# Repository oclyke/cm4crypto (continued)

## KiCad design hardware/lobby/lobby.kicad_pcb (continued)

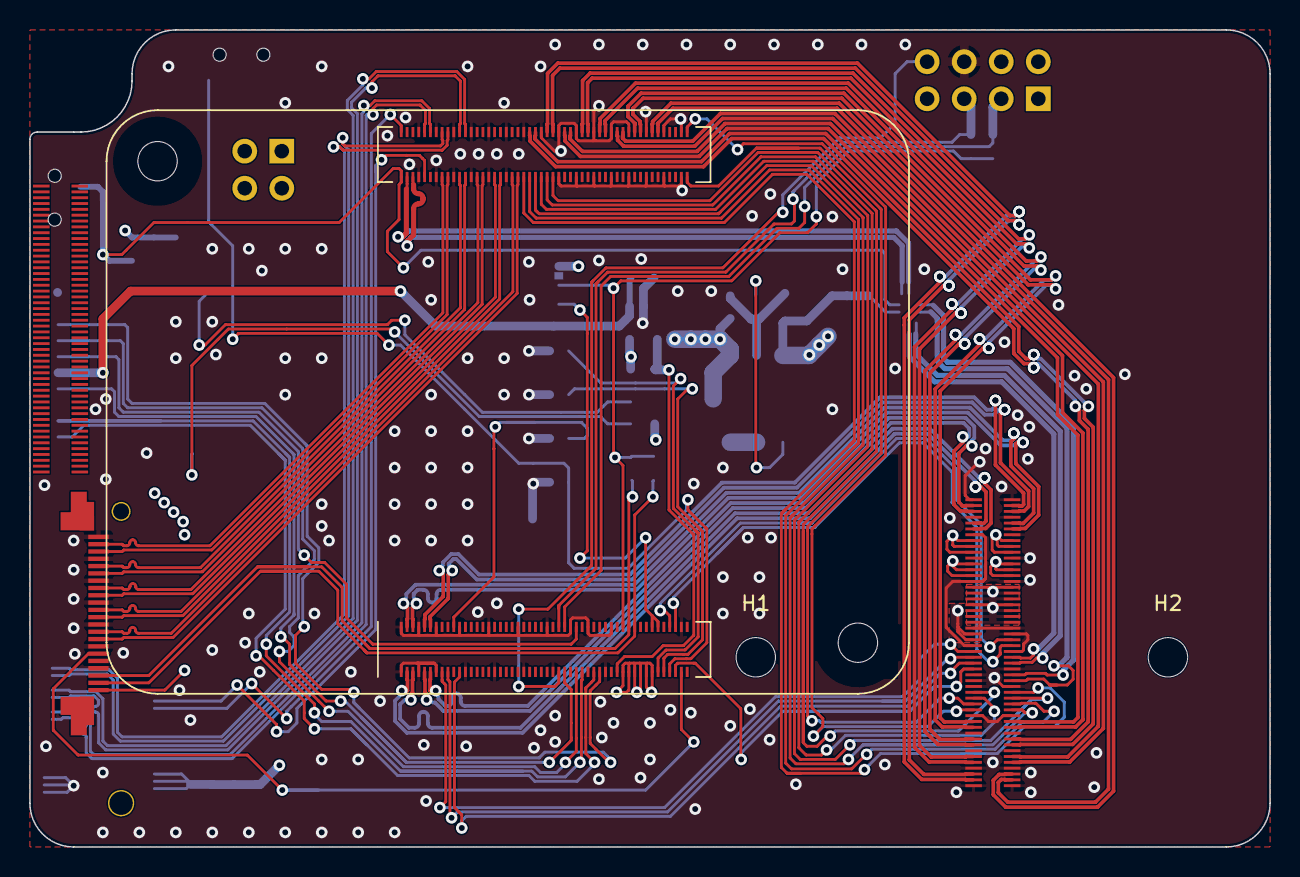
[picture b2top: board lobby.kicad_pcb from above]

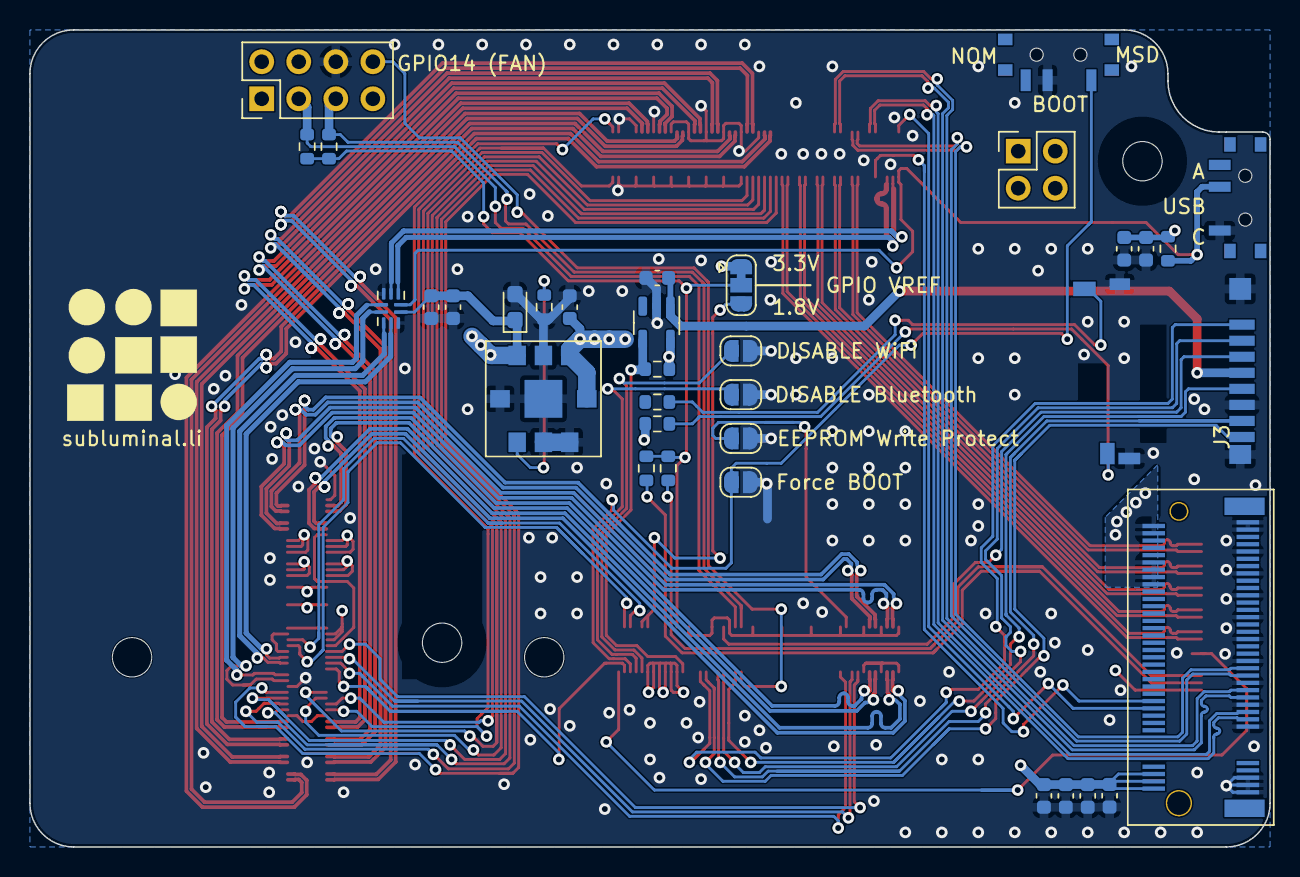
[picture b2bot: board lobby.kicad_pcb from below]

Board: 4 copper layers, 85.0 x 56.0 mm, 40 parts (34 on the bottom side), 93 nets.

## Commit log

2021-05-04 initial commit
    this contains one schematic with pretty much all the necessary bits
    todo: break into two parts for upper and lower pcbs
2021-05-04 initial commit
    planned out project structure and completed schematic for 'lobby' board
    schematic for 'mezzanine' board todo
2021-05-06 start routing mezzanine
    making a progress capture before trying to cram a lot of signals onto just one hirose connector...
2021-05-06 finished mezzanine signal routing
2021-05-13 remove backups
2021-05-13 sheet refs relative, copied escalator pinout to lobby
2021-05-31 move structural hirose connector
    to match location on the lobby board
2021-05-31 work abroad
    did some light planning for the lobby board while on vacation. now ready for final placement + routing
2021-05-31 Update fp-info-cache
    not sure what this is...
2021-05-31 addtl hdmi routing
2021-05-31 Update fp-info-cache
2021-05-31 place lobby components
2021-06-02 attempt to route gpio
2021-06-02 removed gpio from lobby to simplify routing
2021-06-03 finish routing on lobby
2021-06-03 run drc on mezzanine
2021-06-03 update hdmi and usbc footprints for router cut
2021-06-03 adjust USB dp tune
2021-06-03 tweak lobby
    pushed traces for wifi clearance zone
    improved cm4 footprint
    improved usb-c footprint
2021-06-04 tweak mezzanine
    almost ready to order
2021-06-04 update lobby
2021-06-04 update mezzanine
2021-06-04 run cam
2021-06-04 add cam zips
2021-06-07 clean up
2021-06-15 mirror lobby mezzanine connector
    fixing a big whoops
2021-06-15 modify footprints
    add paste on hdmi and usbc
    add silkscreen outline on murata dcdc supply
    change PS cap footprint to polarized footprint
2021-06-15 update silkscreen
2021-06-15 cam v2
2021-07-06 change lobby hirose connectors to the DS variant
2021-07-06 move m.2 adaptor mount hole
2021-07-06 relabel switches
2021-07-07 update camera connector footprint
2021-07-07 update USB-A host capacitor footprint
2021-07-07 regenerate gerbers
2021-07-07 satiate kicad
2021-07-10 update m.2 connector footprint
2021-07-10 change fusb42mx to qfn package
2021-07-10 regenerate cam
2021-07-10 add logo
2021-07-10 regen cam data
2021-07-10 remove footprint silk on logo
2021-07-10 regen gerbers
2021-07-10 hide designators in silk
2021-07-11 add docs
2021-07-11 remove reference hardware
2021-07-29 add poe testing resources
2021-07-29 add variable sample rate
2021-07-29 add heatcam srcs
2021-07-29 Update heatcam_processing.pde
    now handles json format
2021-11-29 pushing local changes
    including prelim docs
2024-04-25 show and tell
2024-04-25 update youtube link
2024-04-25 update video url
